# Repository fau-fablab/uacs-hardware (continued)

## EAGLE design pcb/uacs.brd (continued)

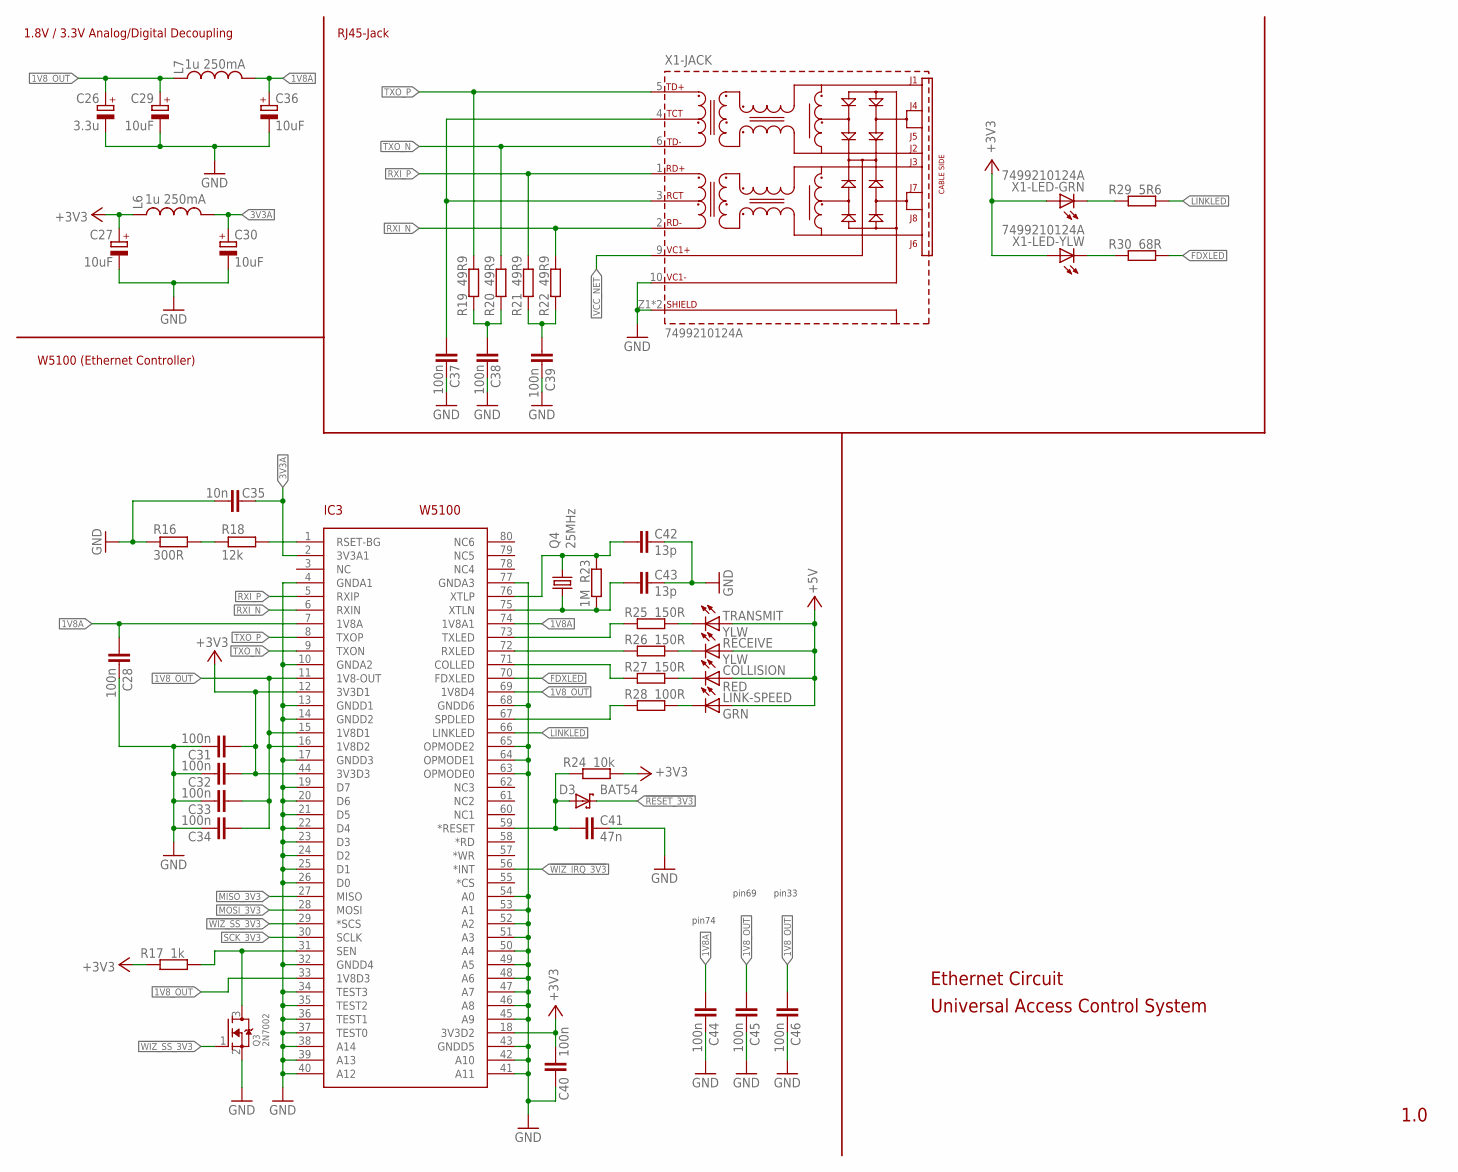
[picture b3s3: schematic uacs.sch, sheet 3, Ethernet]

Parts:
C26: 3.3u; B/3528-21R
C27, C29, C30, C36: 10uF; B/3528-21R
C28, C31, C32, C33, C34, C37, C38, C39, C40, C44, C45, C46: 100n; C0603
C35: 10n; C0603
C41: 47n; C0603
C42, C43: 13p; C0603
COLLISION: RED; CHIPLED_0603
D3: BAT54; SOT23
IC3: W5100; SQFP-S-10X10-80
L6, L7: 1u 250mA; 0603
LINK-SPEED: GRN; CHIPLED_0603
Q3: 2N7002; SOT23
Q4: 25MHz; SM49
R16: 300R; R0603
R17: 1k; R0603
R18: 12k; R0603
R19, R20, R21, R22: 49R9; R0603
R23: 1M; R0603
R24: 10k; R0603
R25, R26, R27: 150R; R0603
R28: 100R; R0603
R29: 5R6; R0603
R30: 68R; R0603
RECEIVE: YLW; CHIPLED_0603
TRANSMIT: YLW; CHIPLED_0603
X1: 7499210124A

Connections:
1V8A: C28.1, C36.+, C44.1, IC3.7 (1V8A), IC3.74 (1V8A1), L7.2
1V8_OUT: C26.+, C29.+, C33.1, C34.1, C45.1, C46.1, IC3.11 (1V8-OUT), IC3.15 (1V8D1), IC3.16 (1V8D2), IC3.33 (1V8D3), IC3.69 (1V8D4), L7.1
3V3A: C30.+, C35.1, IC3.2 (3V3A1), L6.2
!RESET_3V3: D3.3 (C); also elsewhere on the board
!WIZ_IRQ_3V3: IC3.56 (*INT); also elsewhere on the board
!WIZ_SS_3V3: IC3.29 (*SCS), Q3.1 (G); also elsewhere on the board
+3V3: C27.+, C31.1, C32.1, C40.1, IC3.12 (3V3D1), IC3.18 (3V3D2), IC3.44 (3V3D3), L6.1, R17.1, R24.2, X1.12 (A), X1.14 (A); also elsewhere on the board
+5V: COLLISION.A, LINK-SPEED.A, RECEIVE.A, TRANSMIT.A; also elsewhere on the board
FDXLED: IC3.70 (FDXLED), R30.2
GND: C26.-, C27.-, C28.2, C29.-, C30.-, C31.2, C32.2, C33.2, C34.2, C35.2, C36.-, C37.2, C38.2, C39.2, C40.2, C41.2, C42.2, C43.2, C44.2, C45.2, C46.2, IC3.4 (GNDA1), IC3.10 (GNDA2), IC3.13 (GNDD1), IC3.14 (GNDD2), IC3.17 (GNDD3), IC3.19 (D7), IC3.20 (D6), IC3.21 (D5), IC3.22 (D4), IC3.23 (D3), IC3.24 (D2), IC3.25 (D1), IC3.26 (D0), IC3.32 (GNDD4), IC3.34 (TEST3), IC3.35 (TEST2), IC3.36 (TEST1), IC3.37 (TEST0), IC3.38 (A14), IC3.39 (A13), IC3.40 (A12), IC3.41 (A11), IC3.42 (A10), IC3.43 (GNDD5), IC3.45 (A9), IC3.46 (A8), IC3.47 (A7), IC3.48 (A6), IC3.49 (A5), IC3.50 (A4), IC3.51 (A3), IC3.52 (A2), IC3.53 (A1), IC3.54 (A0), IC3.63 (OPMODE0), IC3.64 (OPMODE1), IC3.65 (OPMODE2), IC3.68 (GNDD6), IC3.77 (GNDA3), Q3.2 (S), R16.1, X1.10 (VC1-), X1.Z1 (SHIELD), X1.Z2 (SHIELD); also elsewhere on the board
LINKLED: IC3.66 (LINKLED), R29.2
MISO_3V3: IC3.27 (MISO); also elsewhere on the board
MOSI_3V3: IC3.28 (MOSI); also elsewhere on the board
unnamed: IC3.1 (RSET-BG), R18.2
unnamed: R30.1, X1.13 (C)
unnamed: R29.1, X1.11 (C)
unnamed: C41.1, D3.1 (A), IC3.59 (*RESET), R24.1
unnamed: C39.1, R21.1, R22.1
unnamed: R25.2, TRANSMIT.C
unnamed: C38.1, R19.1, R20.1
unnamed: IC3.67 (SPDLED), R28.1
unnamed: R26.2, RECEIVE.C
unnamed: IC3.71 (COLLED), R27.1
unnamed: IC3.72 (RXLED), R26.1
unnamed: IC3.73 (TXLED), R25.1
unnamed: COLLISION.C, R27.2
unnamed: LINK-SPEED.C, R28.2
unnamed: C43.1, IC3.75 (XTLN), Q4.1, R23.1
unnamed: C42.1, IC3.76 (XTLP), Q4.2, R23.2
unnamed: R16.2, R18.1
RXI_N: IC3.6 (RXIN), R22.2, X1.2 (RD-)
RXI_P: IC3.5 (RXIP), R21.2, X1.1 (RD+)
SCK_3V3: IC3.30 (SCLK); also elsewhere on the board
SEN: IC3.31 (SEN), Q3.3 (D), R17.2
TXCT: C37.1, X1.3 (RCT), X1.4 (TCT)
TXO_N: IC3.9 (TXON), R20.2, X1.6 (TD-)
TXO_P: IC3.8 (TXOP), R19.2, X1.5 (TD+)
VCC_NET: X1.9 (VC1+); also elsewhere on the board

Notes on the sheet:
1.8V / 3.3V Analog/Digital Decoupling
RJ45-Jack
W5100 (Ethernet Controller)
Ethernet Circuit
1.0
pin74
pin69
pin33
Universal Access Control System

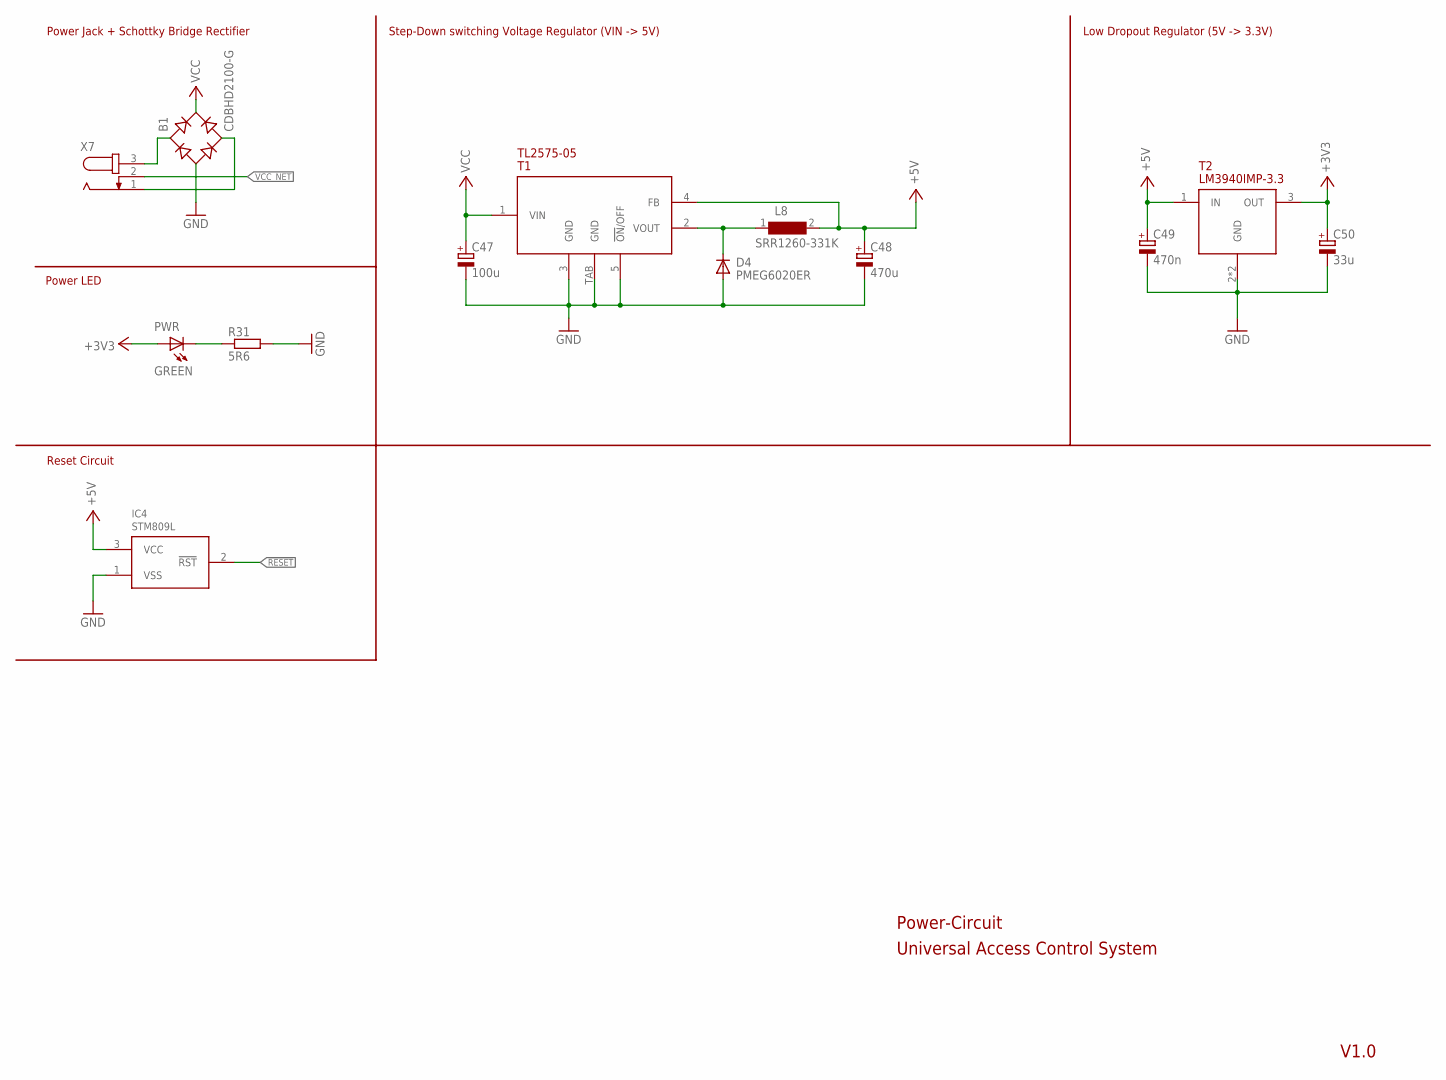
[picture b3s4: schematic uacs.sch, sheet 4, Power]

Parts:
B1: CDBHD2100-G; MBS
C47: 100u; PANASONIC_G
C48: 470u; PANASONIC_G
C49: 470n; PANASONIC_B
C50: 33u; PANASONIC_D
D4: PMEG6020ER; SOD-123
IC4: STM809L; SOT-23-3
L8: SRR1260-331K; WE-PD_1260/1245/1280/1210
PWR: GREEN; CHIPLED_0603
R31: 5R6; R0603
T1: TL2575-05; TO-263-5
T2: LM3940IMP-3.3; SOT223
X7: JACK-PLUG1; SPC4078

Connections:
!RESET: IC4.2 (!RST); also elsewhere on the board
+3V3: C50.+, PWR.A, T2.3 (OUT); also elsewhere on the board
+5V: C48.+, C49.+, IC4.3 (VCC), L8.2, T1.4 (FB), T2.1 (IN); also elsewhere on the board
GND: B1.-, C47.-, C48.-, C49.-, C50.-, D4.A, IC4.1 (VSS), R31.2, T1.3 (GND), T1.5 (!ON!/OFF), T1.TAB (GND), T2.2 (GND), T2.4 (GND); also elsewhere on the board
unnamed: PWR.C, R31.1
unnamed: B1.AC1, X7.3
unnamed: B1.AC2, X7.1
unnamed: D4.C, L8.1, T1.2 (VOUT)
VCC: B1.+, C47.+, T1.1 (VIN)
VCC_NET: X7.2; also elsewhere on the board

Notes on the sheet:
Power Jack + Schottky Bridge Rectifier
Step-Down switching Voltage Regulator (VIN -> 5V)
Low Dropout Regulator (5V -> 3.3V)
Power-Circuit
V1.0
Power LED
Reset Circuit
Universal Access Control System

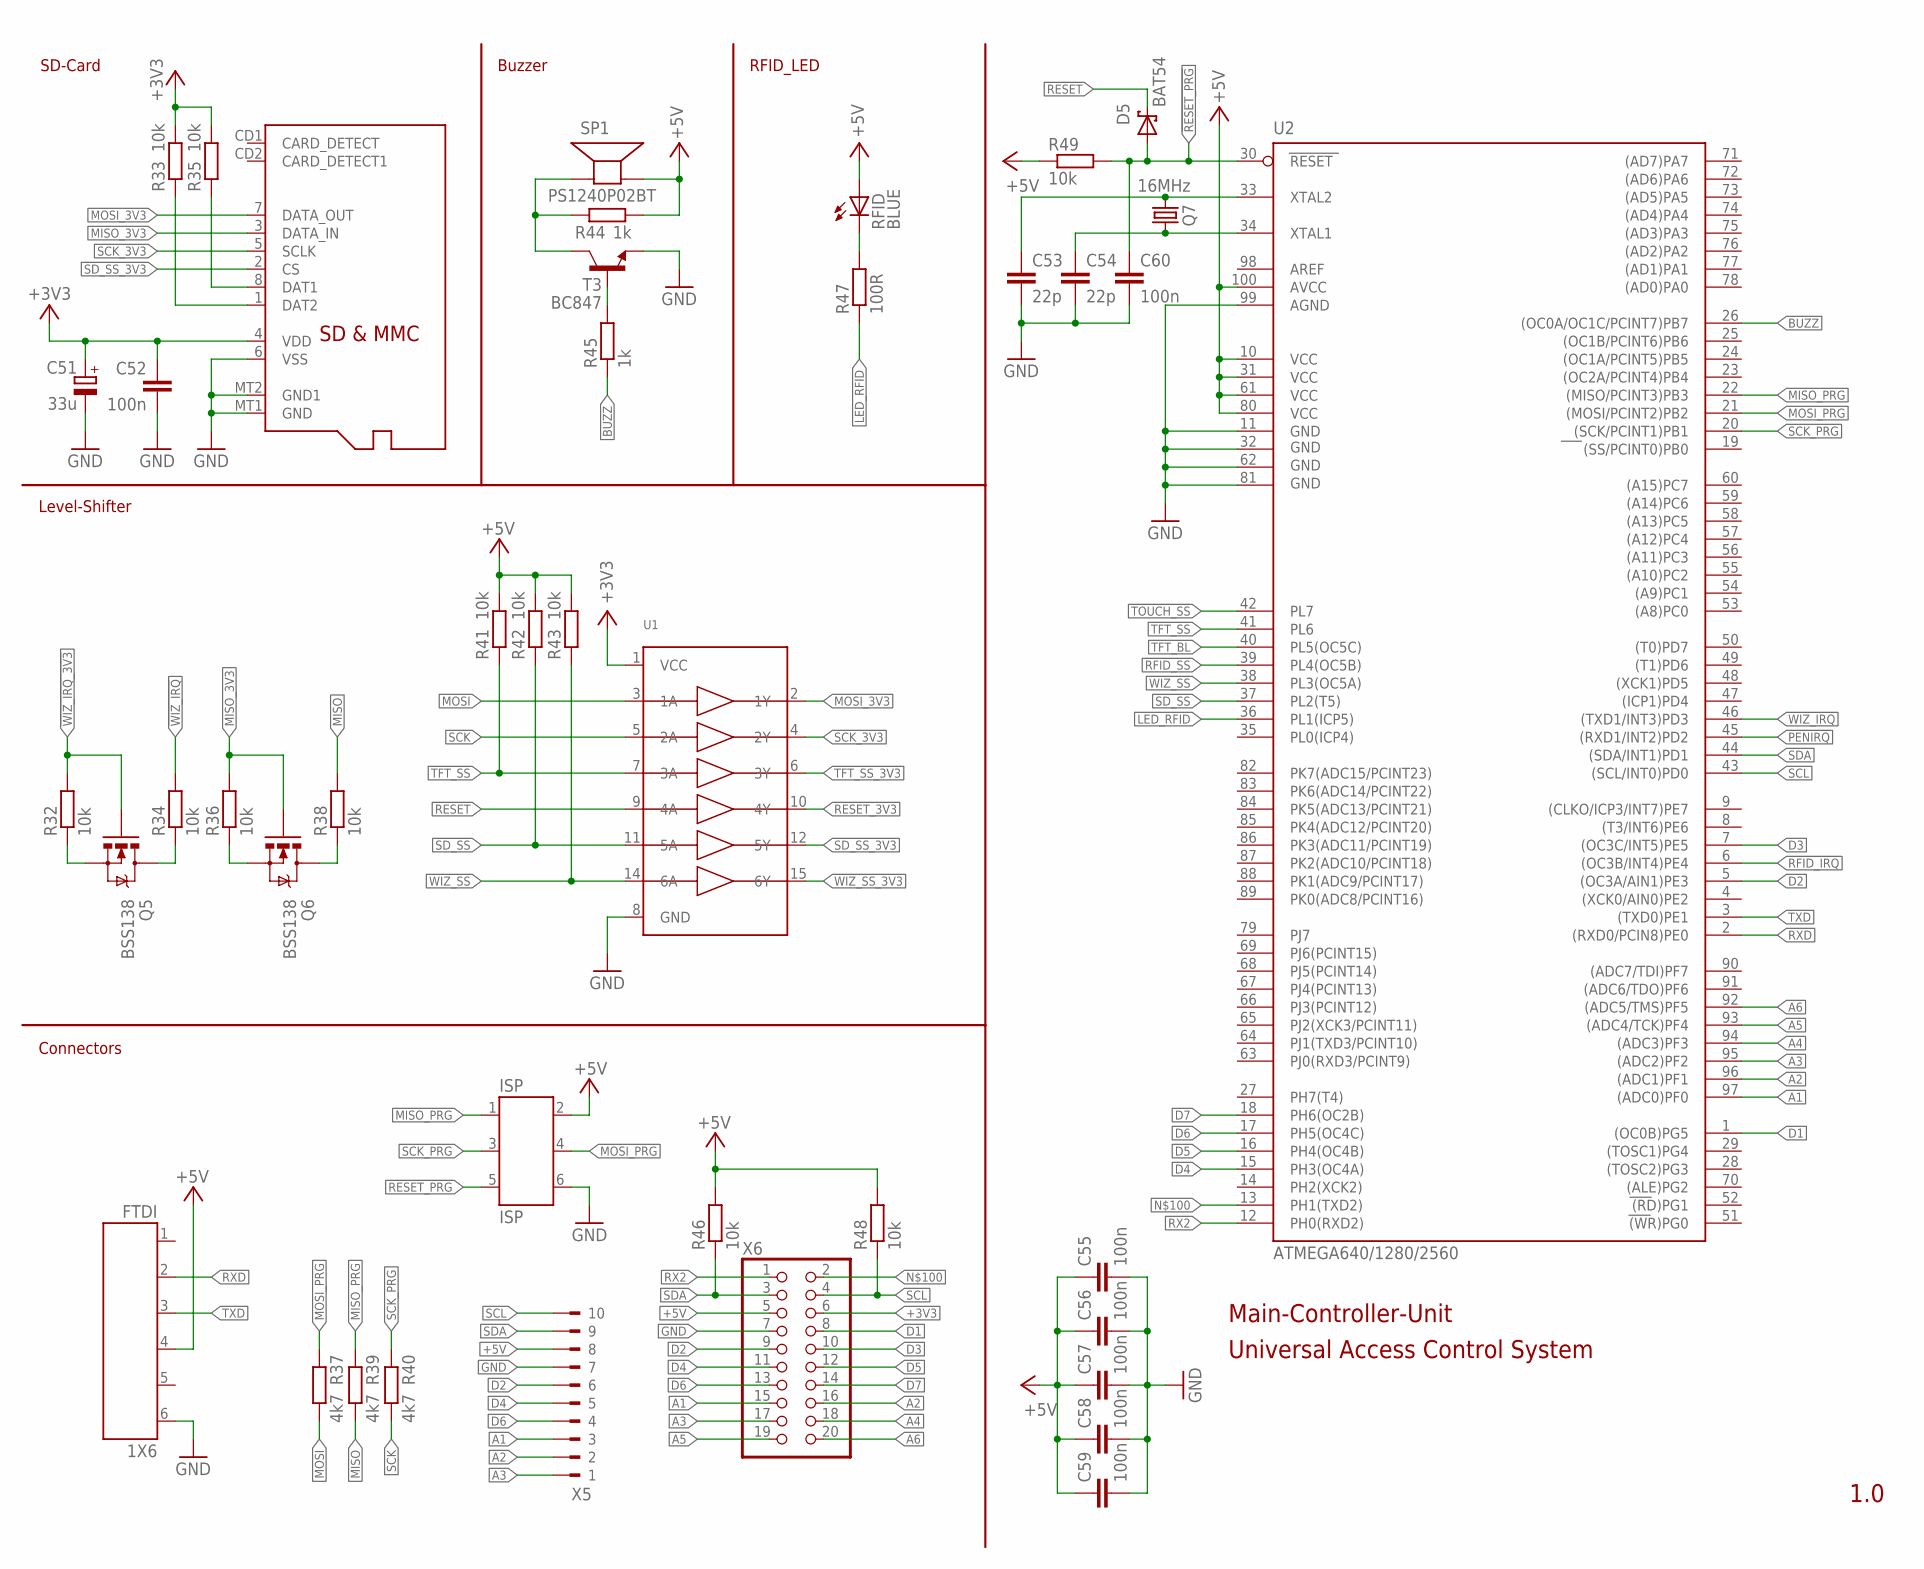
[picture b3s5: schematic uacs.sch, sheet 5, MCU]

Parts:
C51: 33u; C/6032-28R
C52, C55, C56, C57, C58, C59, C60: 100n; C0603
C53, C54: 22p; C0603
D5: BAT54; SOT23
FTDI: 1X6
ISP: ISP; 2X3
Q5, Q6: BSS138; SOT23
Q7: 16MHz; SM49
R32, R33, R34, R35, R36, R38, R41, R42, R43, R46, R48, R49: 10k; R0603
R37, R39, R40: 4k7; R0603
R44, R45: 1k; R0603
R47: 100R; R0603
RFID: BLUE; CHIPLED_0603
SP1: PS1240P02BT; PS12
T3: BC847; SOT23
U1: 74HC4050DTSSOP; TSSOP16
U2: ATMEGA640/1280/2560; TQFP100
X3: MICROSD
X5: 180-10
X6: PINHD-2X10; 2X10

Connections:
!PENIRQ: U2.45 ((RXD1/INT2)PD2); also elsewhere on the board
!RESET: D5.3 (C), U1.9 (4A); also elsewhere on the board
!RESET_3V3: U1.10 (4Y); also elsewhere on the board
!RESET_PRG: C60.1, D5.1 (A), ISP.5, R49.2, U2.30 (RESET)
!RFID_IRQ: U2.6 ((OC3B/INT4)PE4); also elsewhere on the board
!RFID_SS: U2.39 (PL4(OC5B)); also elsewhere on the board
!SD_SS: R42.1, U1.11 (5A), U2.37 (PL2(T5))
!SD_SS_3V3: U1.12 (5Y), X3.2 (CS)
!TFT_SS: R41.1, U1.7 (3A), U2.41 (PL6)
!TFT_SS_3V3: U1.6 (3Y); also elsewhere on the board
!TOUCH_SS: U2.42 (PL7); also elsewhere on the board
!WIZ_IRQ: R34.2, U2.46 ((TXD1/INT3)PD3)
!WIZ_IRQ_3V3: Q5.1 (G), R32.2; also elsewhere on the board
!WIZ_SS: R43.1, U1.14 (6A), U2.38 (PL3(OC5A))
!WIZ_SS_3V3: U1.15 (6Y); also elsewhere on the board
+3V3: C51.+, C52.1, R33.2, R35.2, U1.1 (VCC), X3.4 (VDD), X6.6; also elsewhere on the board
+5V: C55.1, C56.1, C57.1, C58.1, C59.1, FTDI.4, ISP.2, R41.2, R42.2, R43.2, R44.2, R46.2, R48.2, R49.1, RFID.A, SP1.P$2 (-), U2.10 (VCC), U2.31 (VCC1), U2.61 (VCC2), U2.80 (VCC3), U2.100 (AVCC), X5.8, X6.5; also elsewhere on the board
A1: U2.97 ((ADC0)PF0), X5.3, X6.15
A2: U2.96 ((ADC1)PF1), X5.2, X6.16
A3: U2.95 ((ADC2)PF2), X5.1, X6.17
A4: U2.94 ((ADC3)PF3), X6.18
A5: U2.93 ((ADC4/TCK)PF4), X6.19
A6: U2.92 ((ADC5/TMS)PF5), X6.20
BUZZ: R45.1, U2.26 ((OC0A/OC1C/PCINT7)PB7)
D1: U2.1 ((OC0B)PG5), X6.8
D2: U2.5 ((OC3A/AIN1)PE3), X5.6, X6.9
D3: U2.7 ((OC3C/INT5)PE5), X6.10
D4: U2.15 (PH3(OC4A)), X5.5, X6.11
D5: U2.16 (PH4(OC4B)), X6.12
D6: U2.17 (PH5(OC4C)), X5.4, X6.13
D7: U2.18 (PH6(OC2B)), X6.14
GND: C51.-, C52.2, C53.2, C54.2, C55.2, C56.2, C57.2, C58.2, C59.2, C60.2, FTDI.6, ISP.6, T3.2 (E), U1.8 (GND), U2.11 (GND), U2.32 (GND1), U2.62 (GND2), U2.81 (GND3), U2.99 (AGND), X3.6 (VSS), X3.MT1 (GND), X3.MT2 (GND1), X5.7, X6.7; also elsewhere on the board
LED_RFID: R47.1, U2.36 (PL1(ICP5))
MISO: R38.2, R39.2; also elsewhere on the board
MISO_3V3: Q6.1 (G), R36.2, X3.3 (DATA_IN); also elsewhere on the board
MISO_PRG: ISP.1, R39.1, U2.22 ((MISO/PCINT3)PB3)
MOSI: R37.2, U1.3 (1A); also elsewhere on the board
MOSI_3V3: U1.2 (1Y), X3.7 (DATA_OUT); also elsewhere on the board
MOSI_PRG: ISP.4, R37.1, U2.21 ((MOSI/PCINT2)PB2)
unnamed: R47.2, RFID.C
unnamed: C54.1, Q7.1, U2.34 (XTAL1)
unnamed: C53.1, Q7.2, U2.33 (XTAL2)
unnamed: R35.1, X3.8 (DAT1)
unnamed: R44.1, SP1.P$1 (+), T3.3 (C)
unnamed: R45.2, T3.1 (B)
unnamed: Q6.3 (D), R38.1
unnamed: Q6.2 (S), R36.1
unnamed: Q5.2 (S), R32.1
unnamed: Q5.3 (D), R34.1
unnamed: R33.1, X3.1 (DAT2)
unnamed: U2.13 (PH1(TXD2)), X6.2
RX2: U2.12 (PH0(RXD2)), X6.1
RXD: FTDI.2, U2.2 ((RXD0/PCIN8)PE0)
SCK: R40.2, U1.5 (2A); also elsewhere on the board
SCK_3V3: U1.4 (2Y), X3.5 (SCLK); also elsewhere on the board
SCK_PRG: ISP.3, R40.1, U2.20 ((SCK/PCINT1)PB1)
SCL: R48.1, U2.43 ((SCL/INT0)PD0), X5.10, X6.4
SDA: R46.1, U2.44 ((SDA/INT1)PD1), X5.9, X6.3
TFT_BL: U2.40 (PL5(OC5C)); also elsewhere on the board
TXD: FTDI.3, U2.3 ((TXD0)PE1)

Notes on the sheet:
Main-Controller-Unit
1.0
SD-Card
Buzzer
Level-Shifter
RFID_LED
Connectors
Universal Access Control System

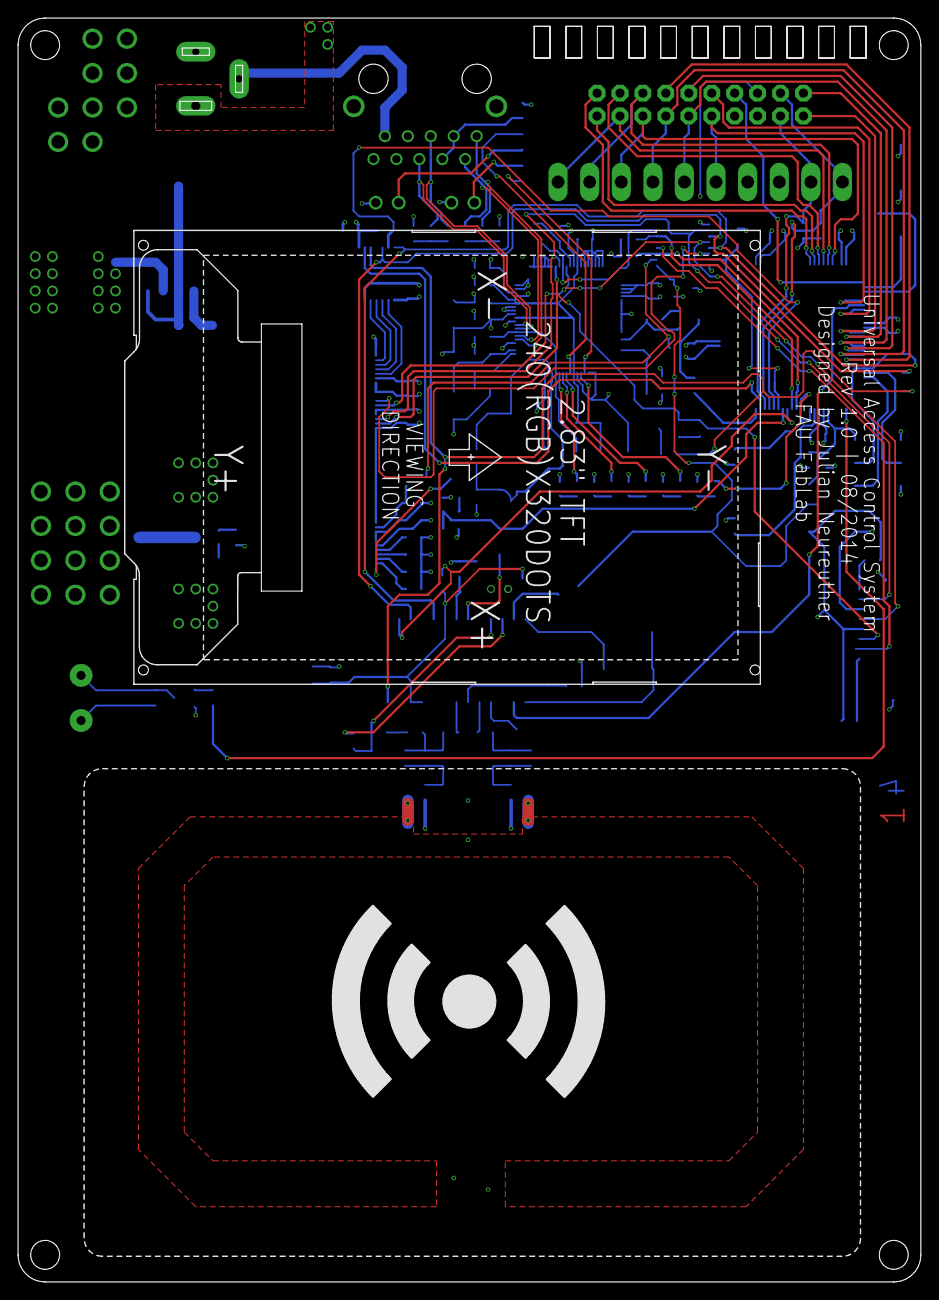
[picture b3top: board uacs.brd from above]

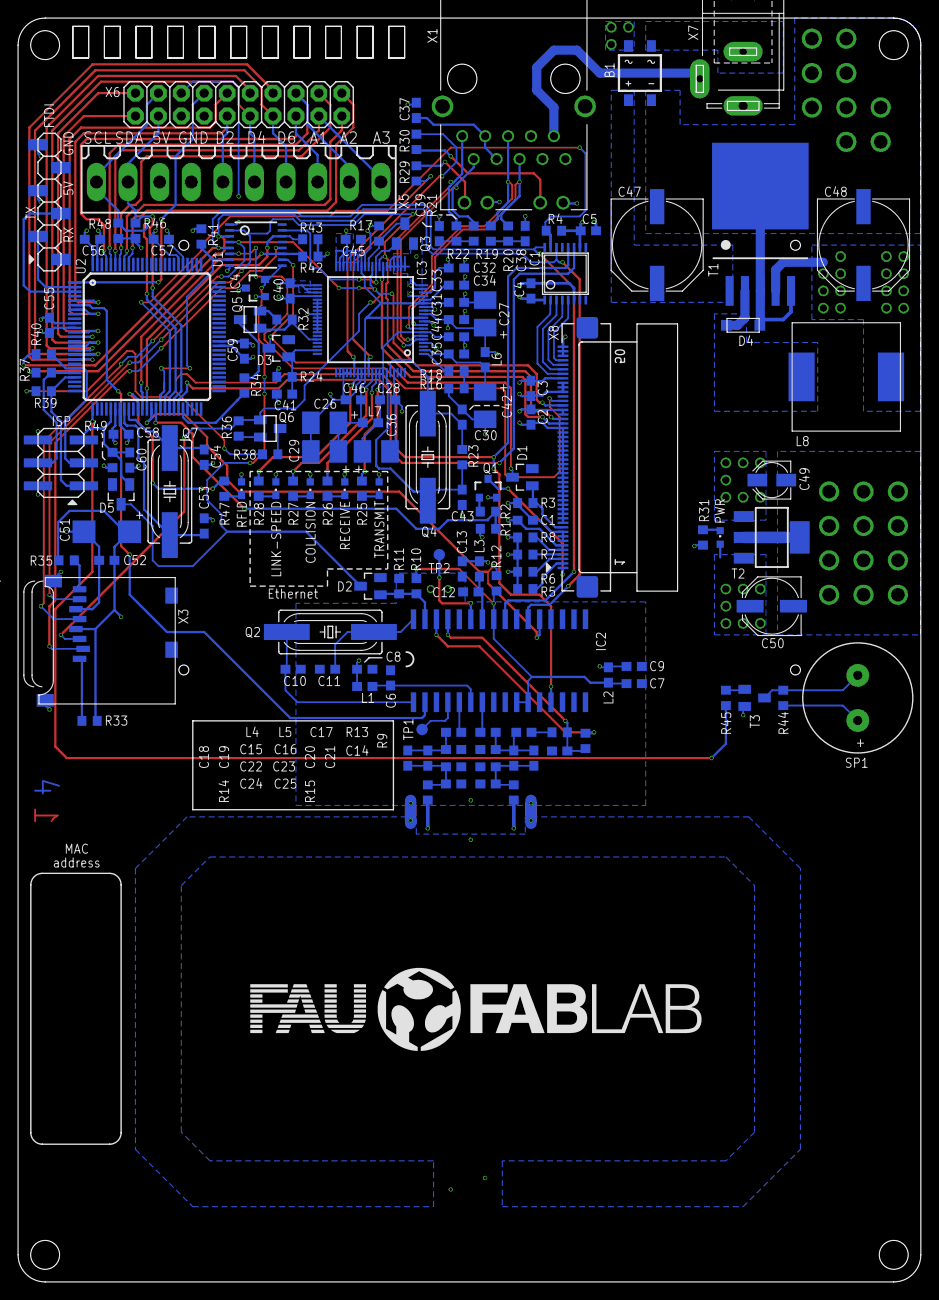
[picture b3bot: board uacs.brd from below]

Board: 4 copper layers, 100.0 x 140.0 mm, 156 parts (155 on the bottom side), 122 nets.

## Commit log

2014-12-10 initial commit v2.0
2014-12-10 add gitignore
2014-12-10 add readme, license, datasheet for pn532. remove old mfrc531 datasheet
2014-12-10 corrected links in readme
2015-04-09 move to kicad
2015-04-09 ignore postscript
2015-04-09 force gitignore
